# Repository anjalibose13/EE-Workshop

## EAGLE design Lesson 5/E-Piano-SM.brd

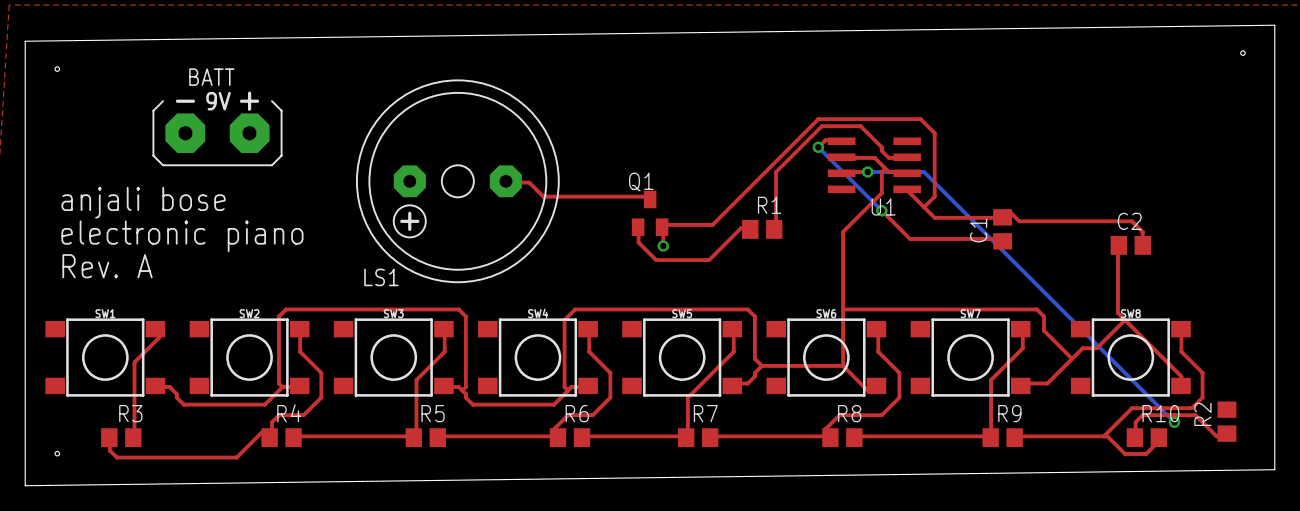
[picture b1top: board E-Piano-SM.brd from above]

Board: 2 copper layers, 99.0 x 36.5 mm, 24 parts (0 on the bottom side), 16 nets.

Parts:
BATT: AB9V
C1, C2: 0.1uF; C0805
LS1: F/HMB
Q1: BCW66; SOT23-BEC
R1, R2, R7: 1K; R0805
R3: 1.5K; R0805
R4: 1.3K; R0805
R5: 620; R0805
R6: 1.1K; R0805
R8: 910; R0805
R9: 390; R0805
R10: 6.2K; R0805
SW1, SW2, SW3, SW4, SW5, SW6, SW7, SW8: MOMENTARY-SWITCH-SPST-SMD-6.2MM-TALL; TACTILE_SWITCH_SMD_6.2MM_TALL
U1: NE555D; SO08

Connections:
0: BATT.-, C1.2, C2.2, Q1.E, U1.1
unnamed: R9.2, R10.2, SW8.B2
unnamed: R2.1, R10.1, U1.7
unnamed: R3.1, SW1.B2
unnamed: R8.2, R9.1, SW7.B2
unnamed: R7.2, R8.1, SW6.B2
unnamed: R6.2, R7.1, SW5.B2
unnamed: R5.2, R6.1, SW4.B2
unnamed: R4.2, R5.1, SW3.B2
unnamed: R3.2, R4.1, SW2.B2
unnamed: R1.2, U1.3
unnamed: C1.1, U1.5
unnamed: LS1.-, Q1.C
unnamed: Q1.B, R1.1
TR: C2.1, SW1.A2, SW2.A2, SW3.A2, SW4.A2, SW5.A2, SW6.A2, SW7.A2, SW8.A2, U1.2, U1.6
VCC: BATT.+, LS1.+, R2.2, U1.4, U1.8

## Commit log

2019-06-27 ee piano project
    electrical engineering piano project
2019-06-28 ee workshop

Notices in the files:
parts and their libraries:
SparkFun-Switches: Licensing: Creative Commons ShareAlike 4.0 International - https://creativecommons.org/licenses/by-sa/4.0
